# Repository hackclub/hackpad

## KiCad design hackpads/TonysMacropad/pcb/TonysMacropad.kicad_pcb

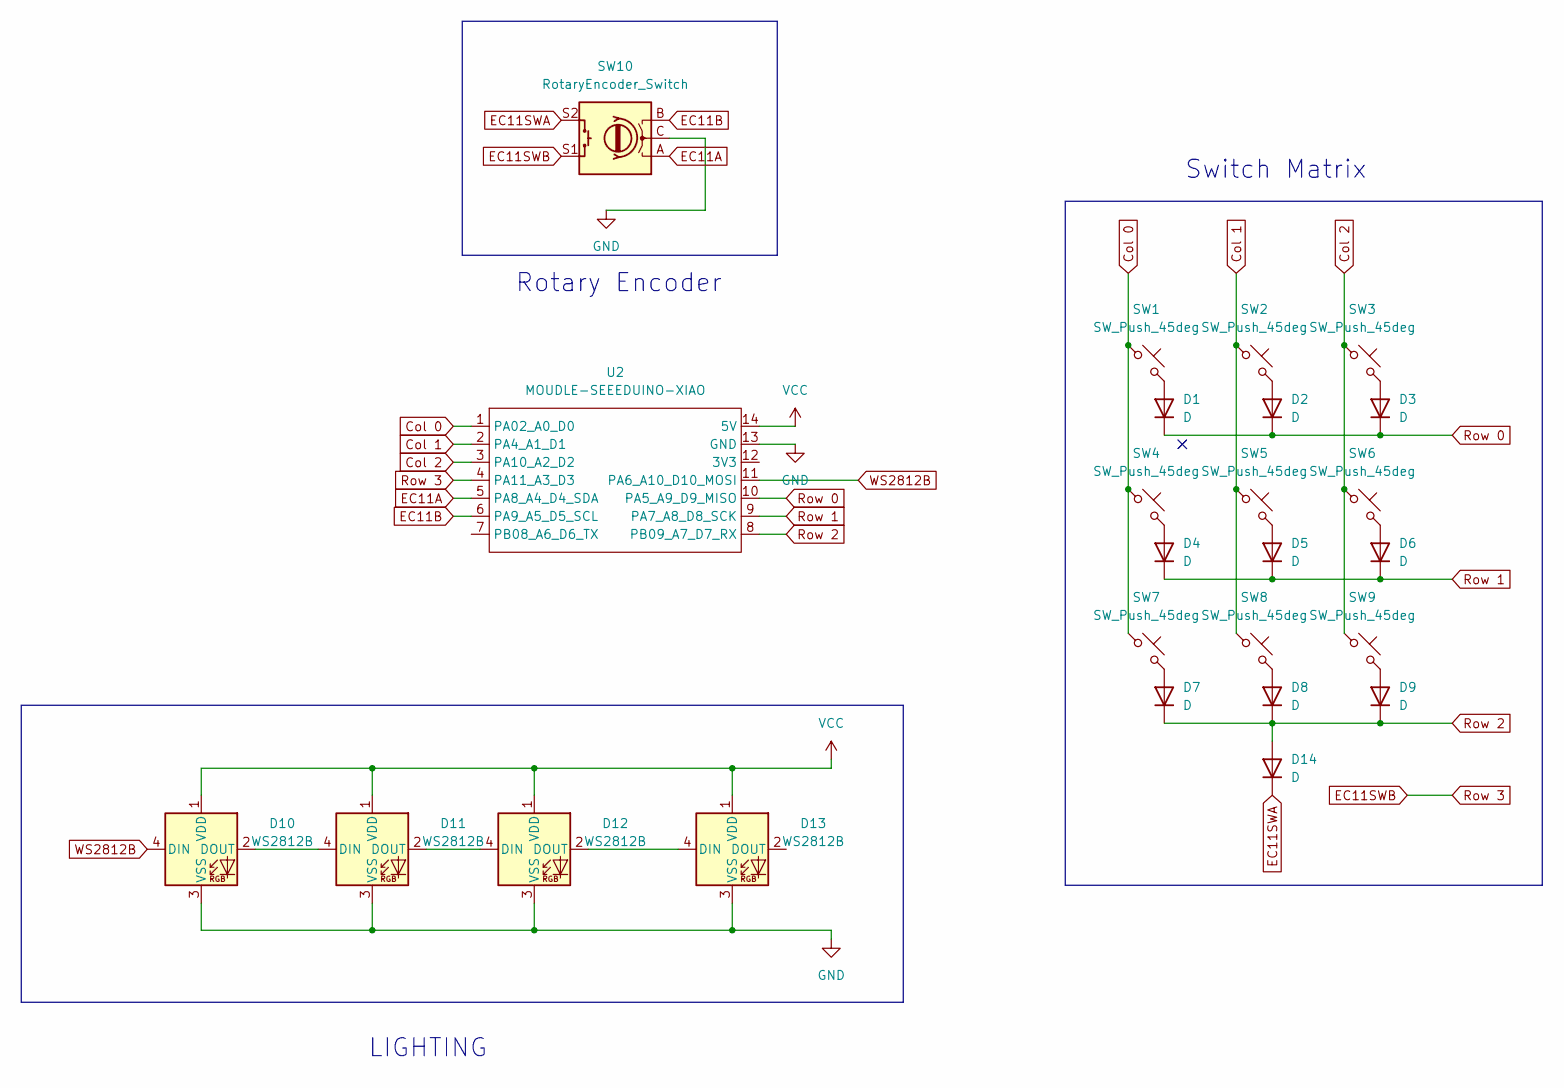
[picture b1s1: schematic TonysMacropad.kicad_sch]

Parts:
D1, D2, D3, D4, D5, D6, D7, D8, D9, D14: D; D_DO-35_SOD27_P7.62mm_Horizontal
D10, D11, D12, D13: WS2812B; LED_WS2812B_PLCC4_5.0x5.0mm_P3.2mm
SW1, SW2, SW3, SW4, SW5, SW6, SW7, SW8, SW9: SW_Push_45deg; SW_Cherry_MX_1.00u_PCB
SW10: RotaryEncoder_Switch; RotaryEncoder_Alps_EC11E-Switch_Vertical_H20mm
U2: MOUDLE-SEEEDUINO-XIAO; XIAO-Generic-Thruhole-14P-2.54-21X17.8MM

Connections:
Col 0: SW1.1, SW4.1, SW7.1, U2.1 (PA02_A0_D0)
Col 1: SW2.1, SW5.1, SW8.1, U2.2 (PA4_A1_D1)
Col 2: SW3.1, SW6.1, SW9.1, U2.3 (PA10_A2_D2)
EC11A: SW10.A, U2.5 (PA8_A4_D4_SDA)
EC11B: SW10.B, U2.6 (PA9_A5_D5_SCL)
EC11SWA: D14.1 (K), SW10.S2
EC11SWB: SW10.S1, U2.4 (PA11_A3_D3)
GND: D10.3 (VSS), D11.3 (VSS), D12.3 (VSS), D13.3 (VSS), SW10.C, U2.13 (GND)
unnamed: D1.2 (A), SW1.2
unnamed: D2.2 (A), SW2.2
unnamed: D3.2 (A), SW3.2
unnamed: D4.2 (A), SW4.2
unnamed: D5.2 (A), SW5.2
unnamed: D6.2 (A), SW6.2
unnamed: D7.2 (A), SW7.2
unnamed: D8.2 (A), SW8.2
unnamed: D9.2 (A), SW9.2
unnamed: D10.2 (DOUT), D11.4 (DIN)
unnamed: D11.2 (DOUT), D12.4 (DIN)
unnamed: D12.2 (DOUT), D13.4 (DIN)
Row 0: D1.1 (K), D2.1 (K), D3.1 (K), U2.10 (PA5_A9_D9_MISO)
Row 1: D4.1 (K), D5.1 (K), D6.1 (K), U2.9 (PA7_A8_D8_SCK)
Row 2: D7.1 (K), D8.1 (K), D9.1 (K), D14.2 (A), U2.8 (PB09_A7_D7_RX)
VCC: D10.1 (VDD), D11.1 (VDD), D12.1 (VDD), D13.1 (VDD), U2.14 (5V)
WS2812B: D10.4 (DIN), U2.11 (PA6_A10_D10_MOSI)

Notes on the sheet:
Switch Matrix
Rotary Encoder
LIGHTING

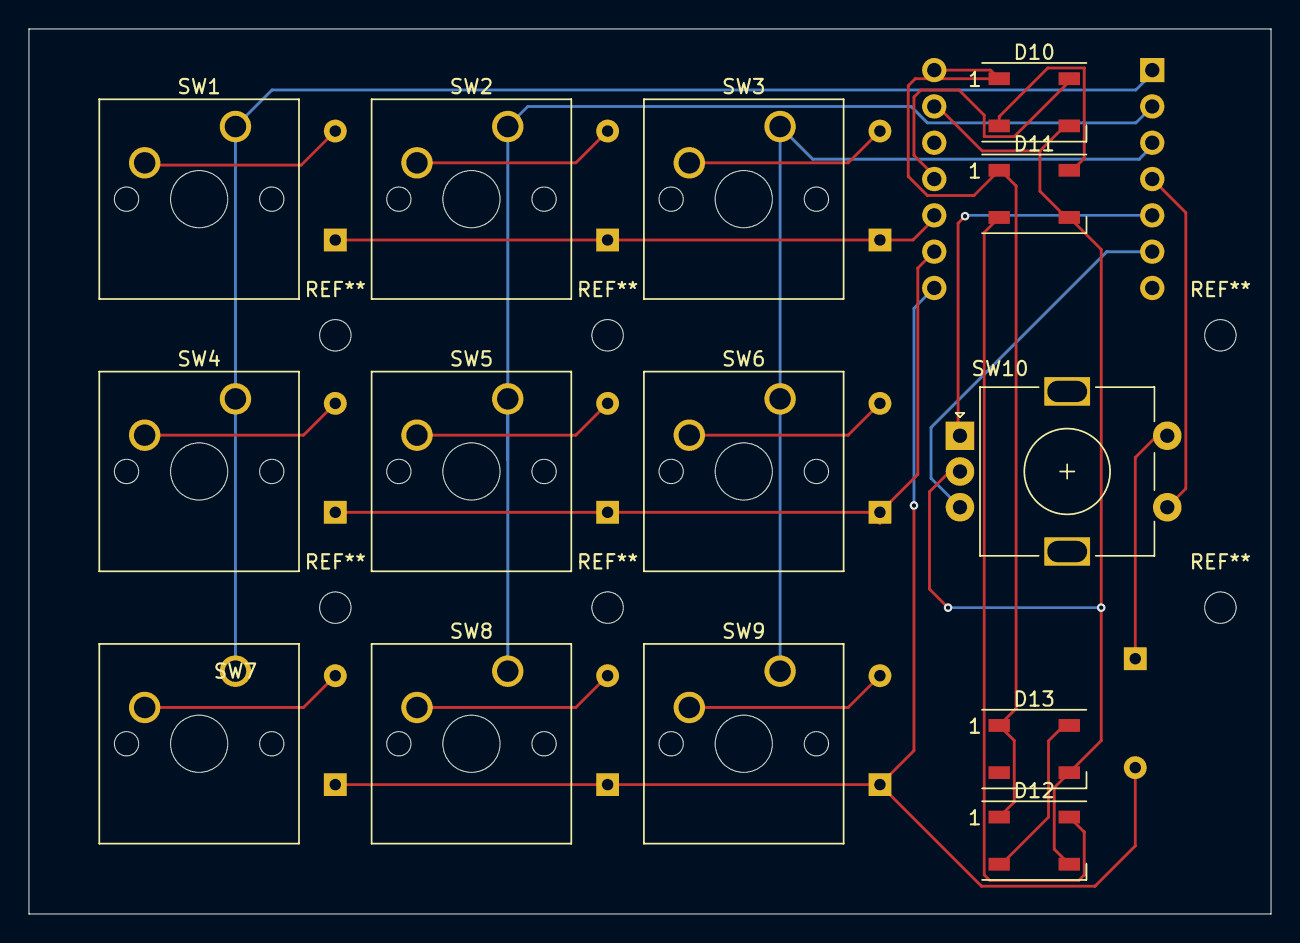
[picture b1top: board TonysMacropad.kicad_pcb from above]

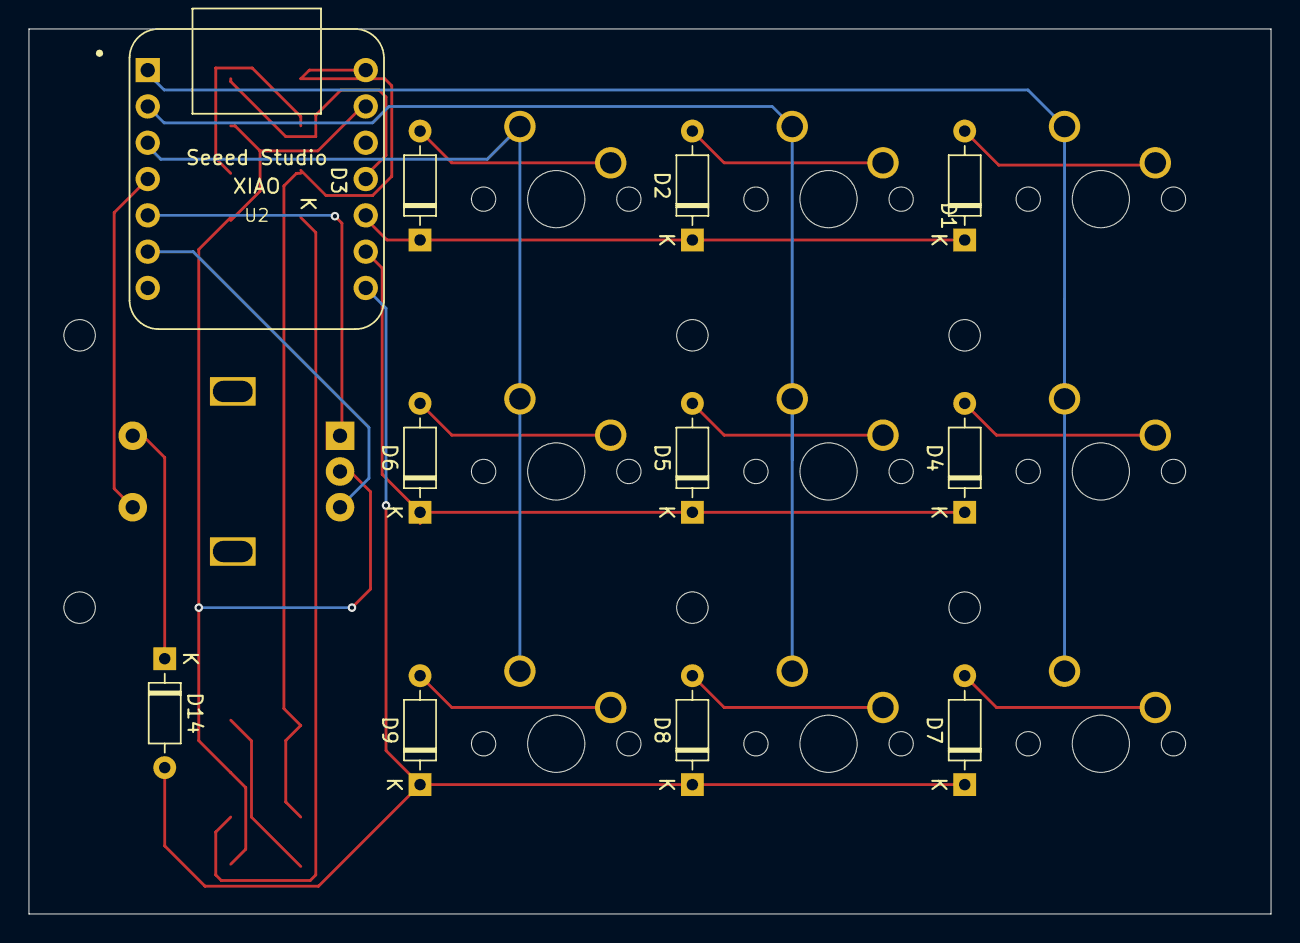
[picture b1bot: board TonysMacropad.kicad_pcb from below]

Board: 2 copper layers, 86.9 x 61.9 mm, 25 parts (11 on the bottom side), 25 nets.

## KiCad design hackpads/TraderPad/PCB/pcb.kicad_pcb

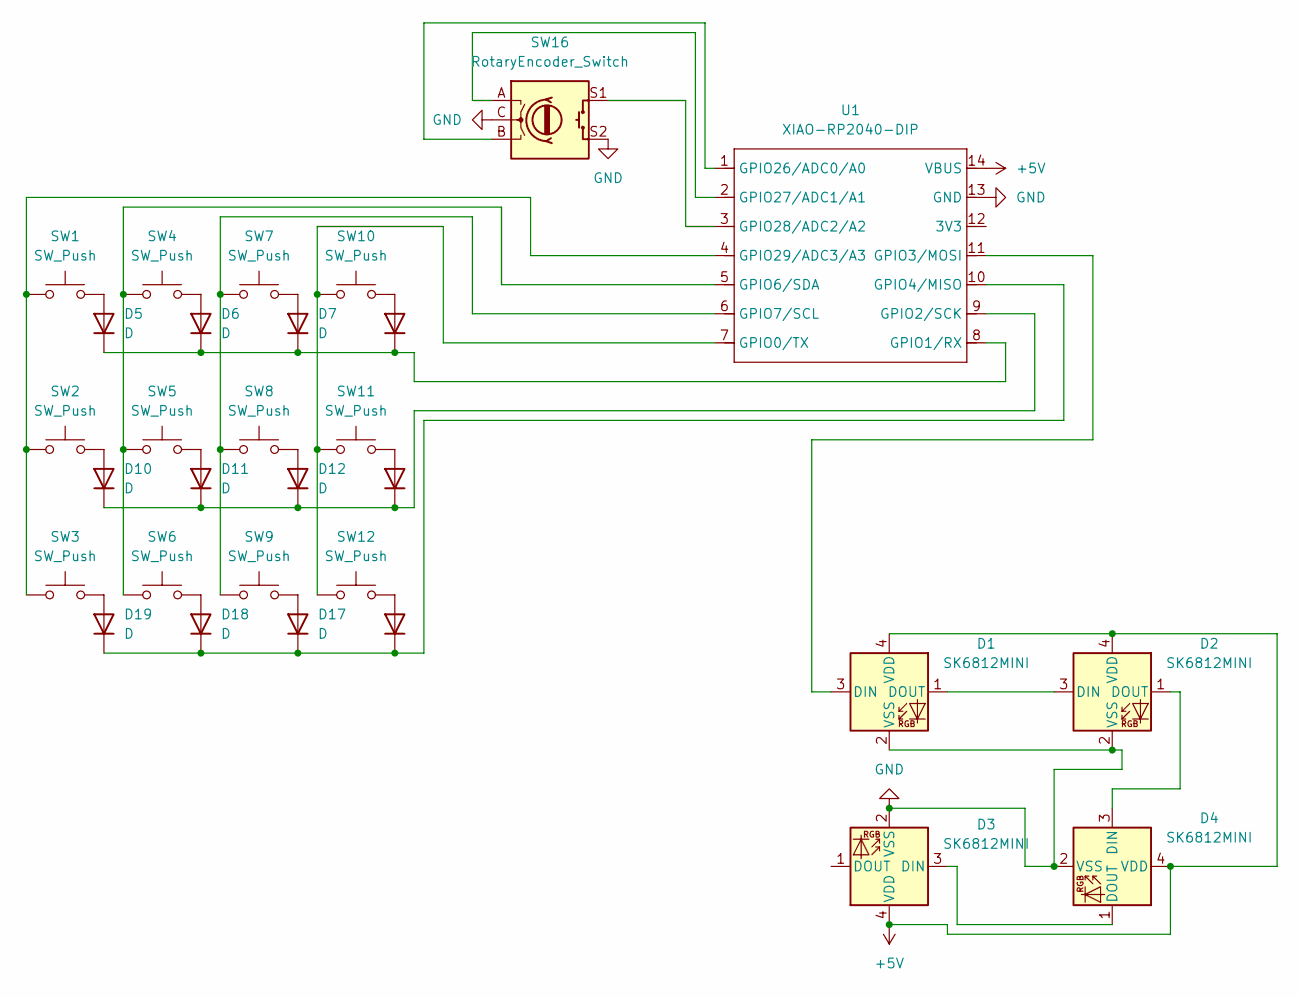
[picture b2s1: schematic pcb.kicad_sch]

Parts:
D1, D2, D3, D4: SK6812MINI; LED_SK6812MINI_PLCC4_3.5x3.5mm_P1.75mm
D5, D6, D7, D8, D10, D11, D12, D13, D16, D17, D18, D19: D; D_DO-35_SOD27_P7.62mm_Horizontal
SW1, SW2, SW3, SW4, SW5, SW6, SW7, SW8, SW9, SW10, SW11, SW12: SW_Push; SW_Cherry_MX_1.00u_PCB
SW16: RotaryEncoder_Switch; RotaryEncoder_Alps_EC11E-Switch_Vertical_H20mm_CircularMoun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
U1: XIAO-RP2040-DIP

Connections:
+5V: D1.4 (VDD), D2.4 (VDD), D3.4 (VDD), D4.4 (VDD), U1.14 (VBUS)
GND: D1.2 (VSS), D2.2 (VSS), D3.2 (VSS), D4.2 (VSS), SW16.C, SW16.S2, U1.13 (GND)
unnamed: D1.3 (DIN), U1.11 (GPIO3/MOSI)
unnamed: D1.1 (DOUT), D2.3 (DIN)
unnamed: D2.1 (DOUT), D4.3 (DIN)
unnamed: D3.3 (DIN), D4.1 (DOUT)
unnamed: D5.2 (A), SW1.2
unnamed: D5.1 (K), D6.1 (K), D7.1 (K), D8.1 (K), U1.8 (GPIO1/RX)
unnamed: D6.2 (A), SW4.2
unnamed: D7.2 (A), SW7.2
unnamed: D8.2 (A), SW10.2
unnamed: D10.2 (A), SW2.2
unnamed: D10.1 (K), D11.1 (K), D12.1 (K), D13.1 (K), U1.9 (GPIO2/SCK)
unnamed: D11.2 (A), SW5.2
unnamed: D12.2 (A), SW8.2
unnamed: D13.2 (A), SW11.2
unnamed: D16.2 (A), SW12.2
unnamed: D16.1 (K), D17.1 (K), D18.1 (K), D19.1 (K), U1.10 (GPIO4/MISO)
unnamed: D17.2 (A), SW9.2
unnamed: D18.2 (A), SW6.2
unnamed: D19.2 (A), SW3.2
unnamed: SW10.1, SW11.1, SW12.1, U1.7 (GPIO0/TX)
unnamed: SW4.1, SW5.1, SW6.1, U1.5 (GPIO6/SDA)
unnamed: SW7.1, SW8.1, SW9.1, U1.6 (GPIO7/SCL)
unnamed: SW16.B, U1.1 (GPIO26/ADC0/A0)
unnamed: SW16.A, U1.2 (GPIO27/ADC1/A1)
unnamed: SW16.S1, U1.3 (GPIO28/ADC2/A2)
unnamed: SW1.1, SW2.1, SW3.1, U1.4 (GPIO29/ADC3/A3)

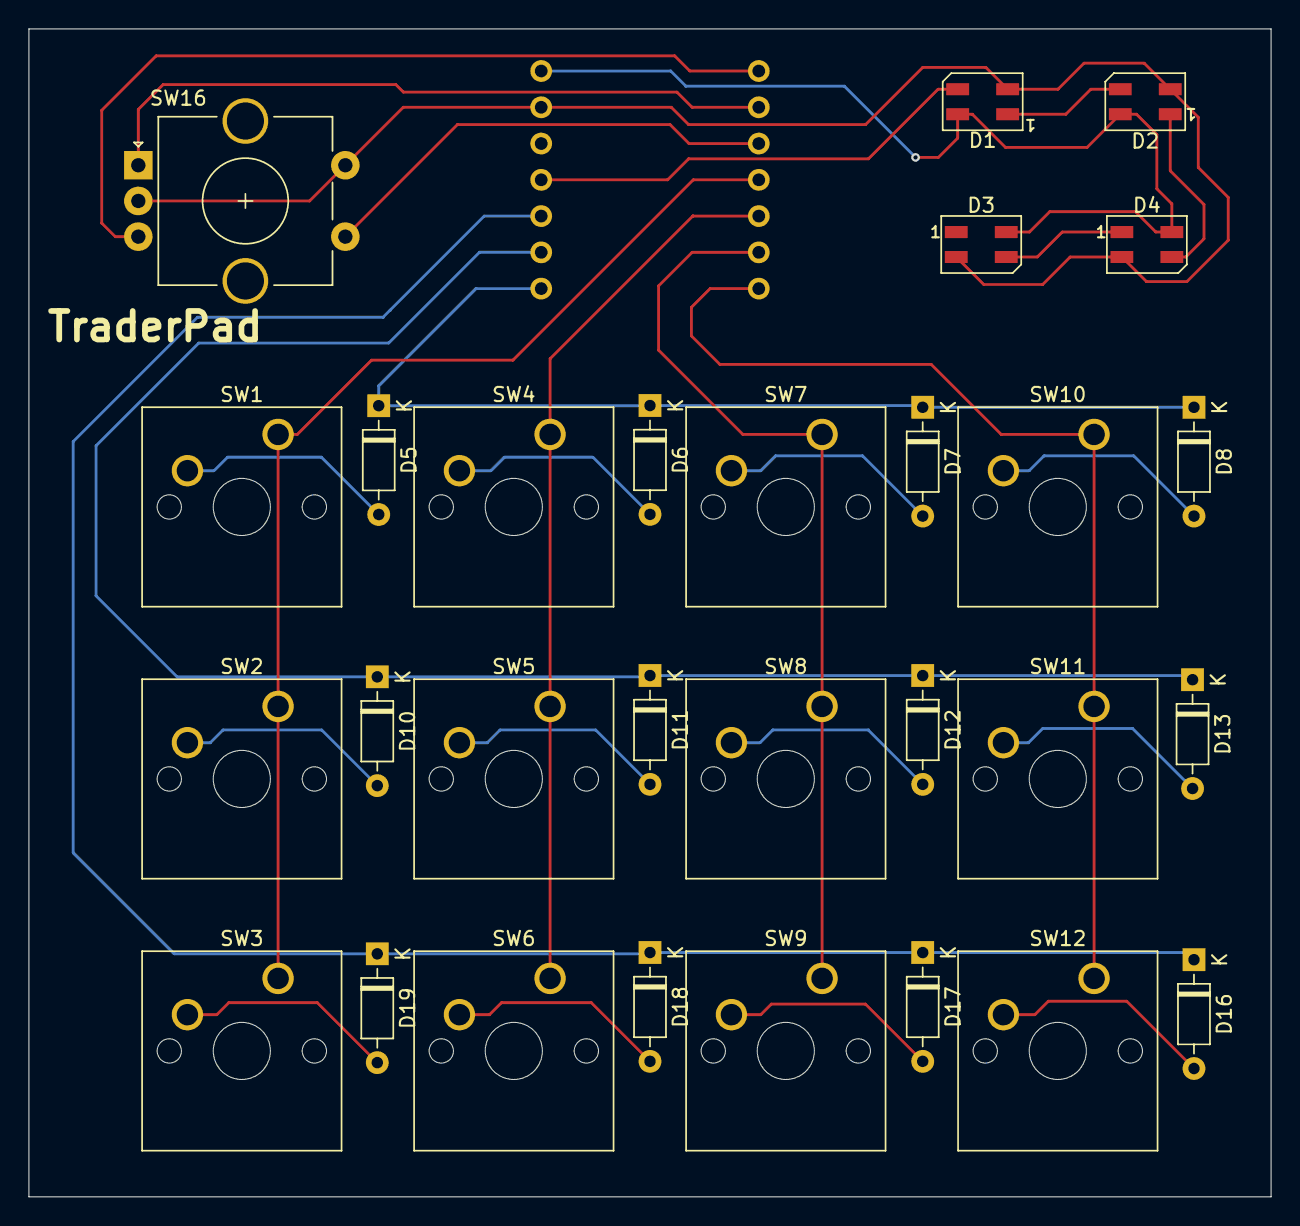
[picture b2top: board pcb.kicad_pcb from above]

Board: 2 copper layers, 87.0 x 81.8 mm, 30 parts (1 on the bottom side), 28 nets.

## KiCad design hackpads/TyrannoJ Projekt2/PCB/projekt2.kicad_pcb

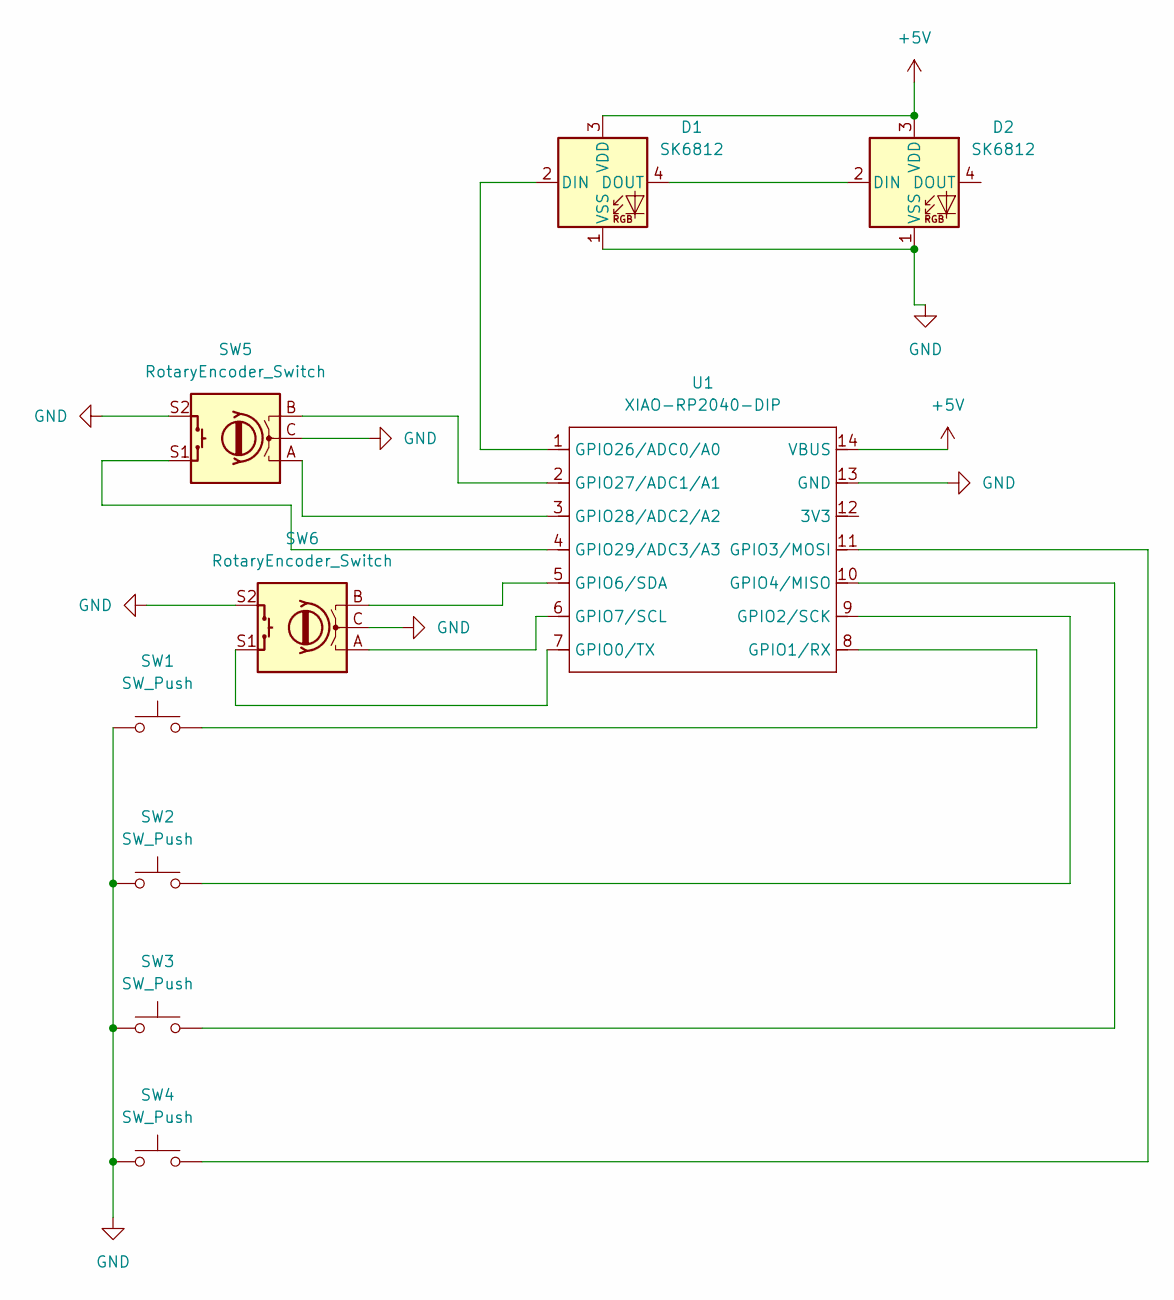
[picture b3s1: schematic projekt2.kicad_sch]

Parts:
D1, D2: SK6812; LED_SK6812MINI_PLCC4_3.5x3.5mm_P1.75mm
SW1, SW2, SW3, SW4: SW_Push; SW_Cherry_MX_1.00u_PCB
SW5, SW6: RotaryEncoder_Switch; RotaryEncoder_Alps_EC11E-Switch_Vertical_H20mm_CircularMoun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
U1: XIAO-RP2040-DIP

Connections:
+5V: D1.3 (VDD), D2.3 (VDD), U1.14 (VBUS)
GND: D1.1 (VSS), D2.1 (VSS), SW1.1, SW2.1, SW3.1, SW4.1, SW5.C, SW5.S2, SW6.C, SW6.S2, U1.13 (GND)
unnamed: D1.2 (DIN), U1.1 (GPIO26/ADC0/A0)
unnamed: D1.4 (DOUT), D2.2 (DIN)
unnamed: SW6.S1, U1.7 (GPIO0/TX)
unnamed: SW1.2, U1.8 (GPIO1/RX)
unnamed: SW2.2, U1.9 (GPIO2/SCK)
unnamed: SW4.2, U1.11 (GPIO3/MOSI)
unnamed: SW3.2, U1.10 (GPIO4/MISO)
unnamed: SW6.B, U1.5 (GPIO6/SDA)
unnamed: SW6.A, U1.6 (GPIO7/SCL)
unnamed: SW5.B, U1.2 (GPIO27/ADC1/A1)
unnamed: SW5.A, U1.3 (GPIO28/ADC2/A2)
unnamed: SW5.S1, U1.4 (GPIO29/ADC3/A3)

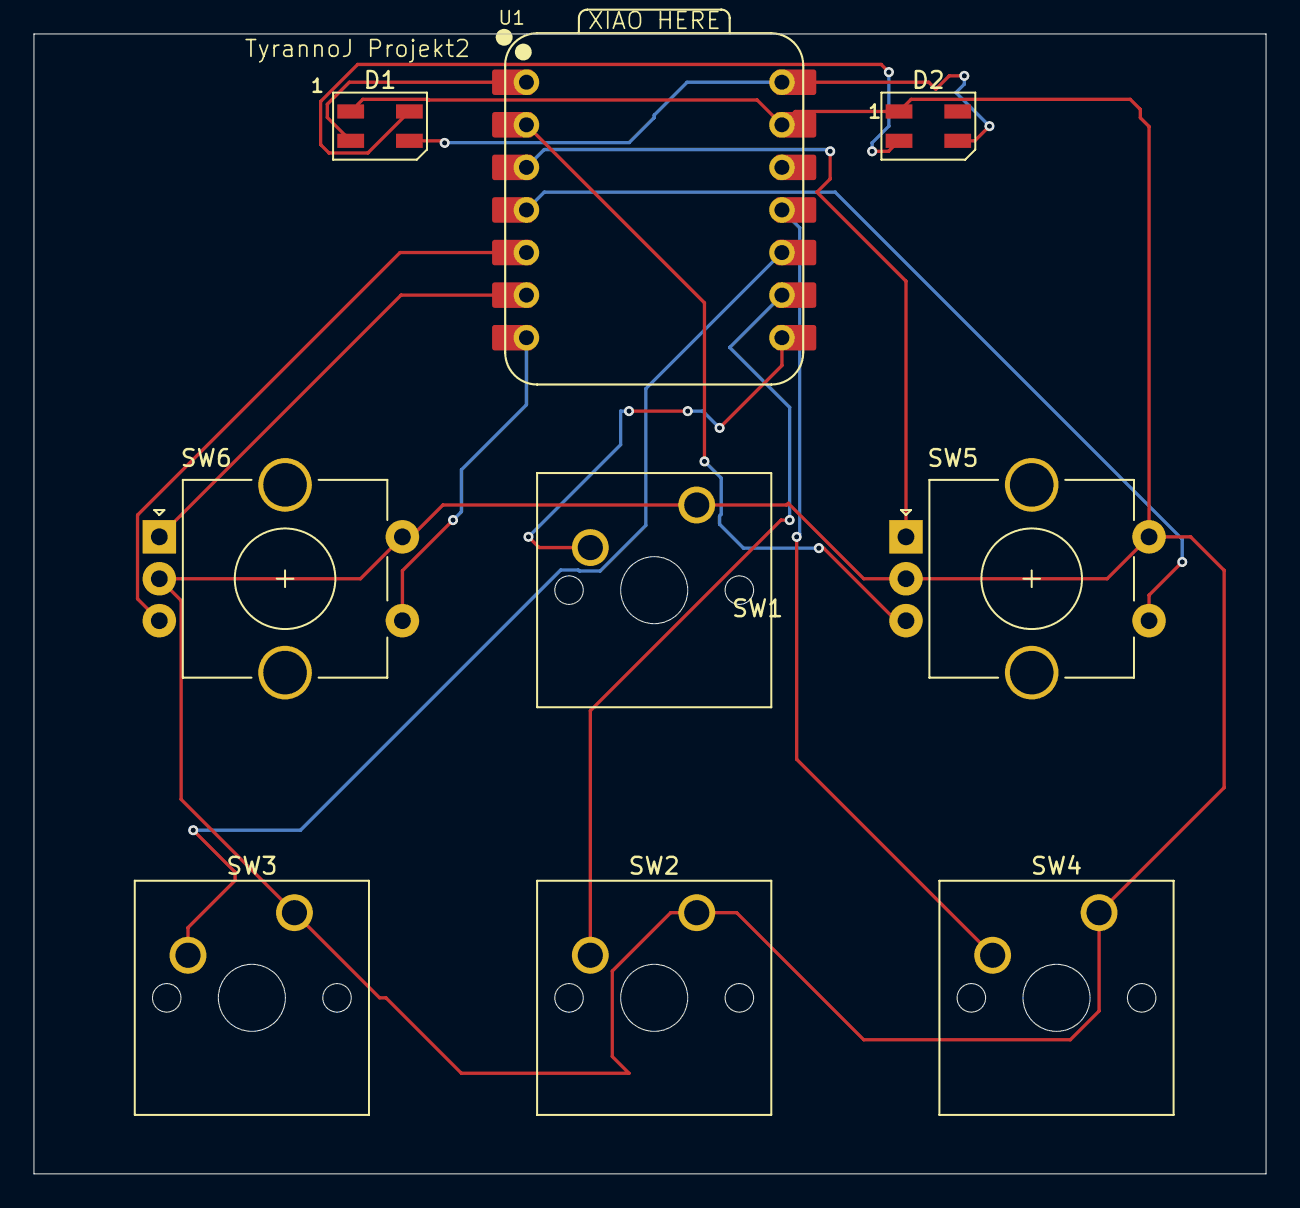
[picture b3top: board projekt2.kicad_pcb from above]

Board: 2 copper layers, 73.5 x 68.0 mm, 9 parts (0 on the bottom side), 14 nets.
